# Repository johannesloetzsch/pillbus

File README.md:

## [PillBus](./hw/stm32)

## License

This source describes Open Hardware and is licensed under the [CERN-OHL-S v2](https://ohwr.org/cern_ohl_s_v2.txt)

Should you produce hardware based on this source, you must where practicable maintain the source location visible on the external case of the products.

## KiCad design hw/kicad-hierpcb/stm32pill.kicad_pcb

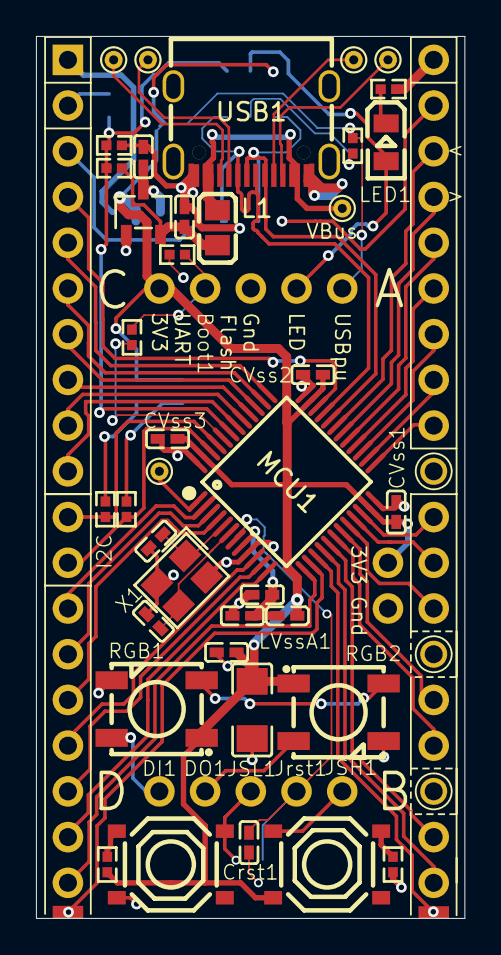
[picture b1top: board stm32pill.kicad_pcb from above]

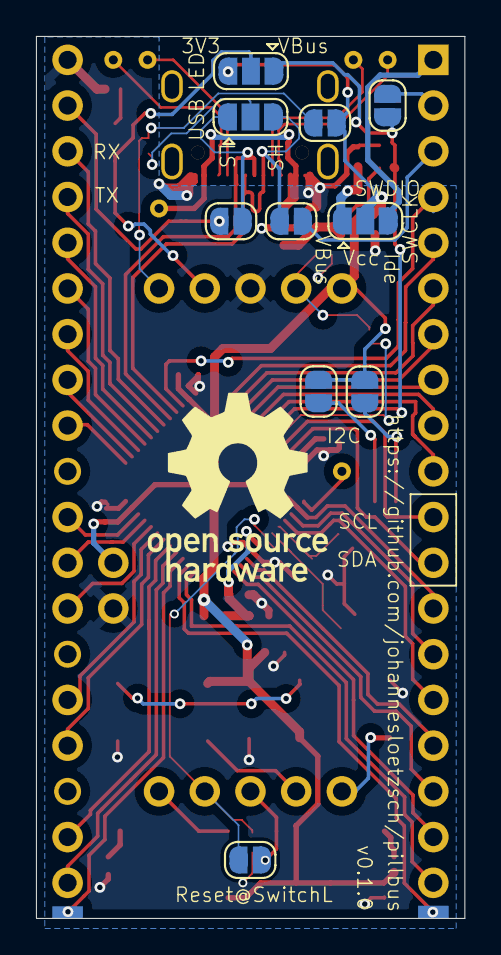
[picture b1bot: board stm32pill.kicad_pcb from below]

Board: 2 copper layers, 23.8 x 49.0 mm, 63 parts (10 on the bottom side), 68 nets.

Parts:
3.3V1: PTH 1.7mm
Boot1: 3x PTH 1.7mm
CC1_1, CC2_1: TestPoint_THTPad_D1.0mm_Drill0.5mm
CLed1: 100nF; C0402
CUin1: 1μF; C0402
CUout1: 1μF; C0402
CVcc1: 4.7uF; C1206
CVss1, CVss2, CVss3: 100nF; C0402
CVssA1: 1μF; C0402
CVssAn1: 10nF; C0402
Cosc1, Cosc2: 30pF; C0402
Crst1: 100nF; C0402
DI1: PTH 1.7mm
DO1: PTH 1.7mm
GND1: PTH 1.7mm
IDE_STM_A1: IDE STM A
IDE_STM_B1: IDE STM B cut
IDE_STM_C1: IDE STM C
IDE_STM_D1: IDE STM D cut
JPLed1: SolderJumper_3_Open; SolderJumper-3_P1.3mm_Open_RoundedPad1.0x1.5mm
JPReset1: SolderJumper_2_Open; SolderJumper-2_P1.3mm_Open_RoundedPad1.0x1.5mm
JPRscl1: SolderJumper_2_Open; SolderJumper-2_P1.3mm_Open_RoundedPad1.0x1.5mm
JPRsda1: SolderJumper_2_Open; SolderJumper-2_P1.3mm_Open_RoundedPad1.0x1.5mm
JPV1: SolderJumper_3_Open; SolderJumper-3_P1.3mm_Open_RoundedPad1.0x1.5mm
JPdn1: SolderJumper_2_Open; SolderJumper-2_P1.3mm_Open_RoundedPad1.0x1.5mm
JPdp1: SolderJumper_2_Open; SolderJumper-2_P1.3mm_Open_RoundedPad1.0x1.5mm
JPpuUSB1: SolderJumper_3_Open; SolderJumper-3_P1.3mm_Open_RoundedPad1.0x1.5mm
JPpuUSBconst1: SolderJumper_2_Open; SolderJumper-2_P1.3mm_Open_RoundedPad1.0x1.5mm
JPvbus1: SolderJumper_2_Open; SolderJumper-2_P1.3mm_Open_RoundedPad1.0x1.5mm
JSH1: PTH 1.7mm
JSL1: PTH 1.7mm
JVbat1: VBAT; TestPoint_THTPad_D1.0mm_Drill0.5mm
Jled1: PTH 1.7mm
JpuUSB1: PTH 1.7mm
Jrst1: PTH 1.7mm
L1: 100Ω@100MHz; L0805
LED1: Green; LED0805-R-RD
LVssA1: 15-30nH; L0402
MCU1: STM32F103C8T6; LQFP-48_L7.0-W7.0-P0.50-LS9.0-BL
RGB1, RGB2: LED WS2812B; LED-SMD_4P-L5.0-W5.0-TL-1
RSBoot1: 51kΩ; R0402
RVbusI1: 51kΩ; R0402
RVbusO1: 100kΩ; R0402
Rled1: 1k-1.5k; R0402
Rpd1: 10kΩ; R0402
Rpu1: 10kΩ; R0402
RpuBoot1: 51kΩ; R0402
RpuUSB1: 1.5kΩ; R0402
Rscl1: 2.2kΩ; R0402
Rsda1: 2.2kΩ; R0402
SBU1_1, SBU2_1: TestPoint_THTPad_D1.0mm_Drill0.5mm
SW1, SW2: Tactile Switch; SW-SMD_4P-L5.1-W5.1-P3.70-LS6.5-TL_H1.5
U1: 3.3V Voltage Regulator 200mA; SOT-23-3_L2.9-W1.6-P1.90-LS2.8-BR
USB1: USB_C; USB-C_SMD-TYPE-C-31-M-12
VBus_1: TestPoint_THTPad_D1.0mm_Drill0.5mm
X1: Crystal 12MHz X322512MSB4SI; CRYSTAL-SMD_4P-L3.2-W2.5-BL

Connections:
+3.3V: 3.3V1.1, Boot1.3, CLed1.2, CVcc1.1, CVss1.2, CVss2.2, CVss3.2, JPLed1.3 (B), JPRscl1.2 (B), JPRsda1.1 (A), JPV1.2 (C), JPpuUSBconst1.2 (B), LVssA1.2, MCU1.23 (VSS_1), MCU1.35 (VSS_2), MCU1.47 (VSS_3), RGB1.1 (VDD), RGB2.1 (VDD), Rpu1.2, SW2.2 (B)
/Boot0: Boot1.2, RSBoot1.2, RpuBoot1.1
/CC1: CC1_1.1, USB1.A5 (CC1)
/CC2: CC2_1.1, USB1.B5 (CC2)
/I2C1 SCL: IDE_STM_D1.SCL (IDE39_STM45), MCU1.45 (PB8), Rscl1.1
/I2C1 SDA: IDE_STM_D1.SDA (IDE37_STM46), MCU1.46 (PB9), Rsda1.1
/I2C2 SCL, USART3 TX: IDE_STM_B1.B1 (IDE24_STM13), MCU1.21 (PB10)
/I2C2 SDA, USART3 RX: IDE_STM_B1.B0 (IDE22_STM14), MCU1.22 (PB11)
/NRST: Crst1.2, JPReset1.1 (A), Jrst1.1, MCU1.7 (NRST)
/OSC_IN: Cosc1.2, MCU1.5 (PD0-OSC_IN), X1.1 (OSC1)
/OSC_OUT: Cosc2.2, MCU1.6 (PD1-OSC_OUT), X1.3 (OSC2)
/SBU1: SBU1_1.1, USB1.A8 (SBU1)
/SBU2: SBU2_1.1, USB1.B8 (SBU2)
/SPI1 MISO: IDE_STM_B1.B6 (IDE38_STM3), MCU1.16 (PA6)
/SPI1 MOSI: IDE_STM_B1.B5 (IDE36_STM4), MCU1.17 (PA7)
/SPI1 SCK: IDE_STM_B1.B7 (IDE40_STM2), MCU1.15 (PA5)
/SPI2 MISO: IDE_STM_A1.A5 (IDE14_STM17), MCU1.27 (PB14)
/SPI2 MOSI: IDE_STM_A1.A4 (IDE12_STM18), MCU1.28 (PB15)
/SPI2 NSS: IDE_STM_A1.A7 (IDE18_STM15), MCU1.25 (PB12)
/SPI2 SCK: IDE_STM_A1.A6 (IDE16_STM16), MCU1.26 (PB13)
/USART1 RX: IDE_STM_A1.A1 (IDE6_STM21), MCU1.31 (PA10)
/USART1 TX: IDE_STM_A1.A2 (IDE8_STM20), MCU1.30 (PA9)
/USB VBusSense: JPLed1.1 (A), JPvbus1.1 (A), MCU1.43 (PB7), RVbusI1.2, RVbusO1.1
/USBd+: JPdp1.2 (B), JPpuUSB1.3 (B), MCU1.33 (PA12), USB1.A6 (DP1), USB1.B6 (DP2)
/USBd-: JPdn1.1 (A), JPpuUSB1.1 (A), MCU1.32 (PA11), USB1.A7 (DN1), USB1.B7 (DN2)
/VBAT: JVbat1.1, MCU1.1 (VBAT)
/VBUS: CUin1.1, L1.1, RVbusI1.1, U1.2 (Vin)
/VSSA: CVssA1.2, CVssAn1.2, LVssA1.1, MCU1.8 (VSSA)
GND: Boot1.1, CLed1.1, CUin1.2, CUout1.2, CVcc1.2, CVss1.1, CVss2.1, CVss3.1, CVssA1.1, CVssAn1.1, Cosc1.1, Cosc2.1, Crst1.1, GND1.1, IDE_STM_A1.GND (IDE2_STM24), MCU1.9 (VDDA), MCU1.24 (VDD_1), MCU1.36 (VDD_2), MCU1.48 (VDD_3), RGB1.3 (GND), RGB2.3 (GND), RVbusO1.2, Rled1.1, Rpd1.1, RpuBoot1.2, SW1.3 (C), U1.1 (GND), USB1.A1 (GND), USB1.A12 (GND), USB1.B1 (GND), USB1.B12 (GND), X1.2 (GND), X1.4 (GND)
unnamed: DI1.1, RGB1.4 (DI)
unnamed: DO1.1, RGB2.2 (DO)
unnamed: IDE_STM_A1.A0 (IDE4_STM22), JPdn1.2 (B)
unnamed: IDE_STM_A1.A3 (IDE10_STM19), MCU1.29 (PA8)
unnamed: IDE_STM_B1.B2 (IDE26_STM12), MCU1.20 (PB2)
unnamed: IDE_STM_B1.B3 (IDE30_STM11), MCU1.19 (PB1)
unnamed: IDE_STM_B1.B4 (IDE32_STM10), MCU1.18 (PB0)
unnamed: IDE_STM_C1.3V3 (IDE1_STM23), JPV1.3 (B)
unnamed: IDE_STM_C1.VBusSense (IDE3_STM43), JPvbus1.2 (B)
unnamed: IDE_STM_C1.C0 (IDE5_STM25), JPdp1.1 (A)
unnamed: IDE_STM_C1.C1 (IDE7_STM26), MCU1.34 (PA13)
unnamed: IDE_STM_C1.C2 (IDE9_STM27), MCU1.37 (PA14)
unnamed: IDE_STM_C1.C3 (IDE11_STM28), MCU1.38 (PA15)
unnamed: IDE_STM_C1.C4 (IDE13_STM29), MCU1.39 (PB3)
unnamed: IDE_STM_C1.C5 (IDE15_STM30), MCU1.40 (PB4)
unnamed: IDE_STM_C1.C6 (IDE17_STM31), MCU1.41 (PB5)
unnamed: IDE_STM_C1.C7 (IDE19_STM32), MCU1.42 (PB6)
unnamed: IDE_STM_D1.D7 (IDE21_STM33), MCU1.14 (PA4)
unnamed: IDE_STM_D1.D6 (IDE23_STM34), MCU1.13 (PA3)
unnamed: IDE_STM_D1.D5 (IDE25_STM37), MCU1.12 (PA2)
unnamed: IDE_STM_D1.D4 (IDE27_STM38), MCU1.11 (PA1)
unnamed: IDE_STM_D1.D3 (IDE29_STM39), MCU1.10 (PA0-WKUP)
unnamed: IDE_STM_D1.D2 (IDE31_STM40), MCU1.4 (PC15-OSC32_OUT)
unnamed: IDE_STM_D1.D1 (IDE33_STM41), MCU1.3 (PC14-OSC32_IN)
unnamed: IDE_STM_D1.D0 (IDE35_STM42), MCU1.2 (PC13-TAMPER-RTC)
unnamed: JPLed1.2 (C), Jled1.1, LED1.1 (A)
unnamed: JPReset1.2 (B), JSL1.1, SW1.2 (B)
unnamed: JPRscl1.1 (A), Rscl1.2
unnamed: JPRsda1.2 (B), Rsda1.2
unnamed: CUout1.1, JPV1.1 (A), U1.3 (Vout)
unnamed: JPpuUSB1.2 (C), RpuUSB1.1
unnamed: JPpuUSBconst1.1 (A), JpuUSB1.1, RpuUSB1.2
unnamed: JSH1.1, SW2.4 (D)
unnamed: LED1.2 (K), Rled1.2
unnamed: MCU1.44 (BOOT0), RSBoot1.1
unnamed: RGB1.2 (DO), RGB2.4 (DI)
unnamed: Rpu1.1, SW1.1 (A)
unnamed: Rpd1.2, SW2.3 (C)
unnamed: L1.2, USB1.A4 (VBUS), USB1.A9 (VBUS), USB1.B4 (VBUS), USB1.B9 (VBUS), VBus_1.1

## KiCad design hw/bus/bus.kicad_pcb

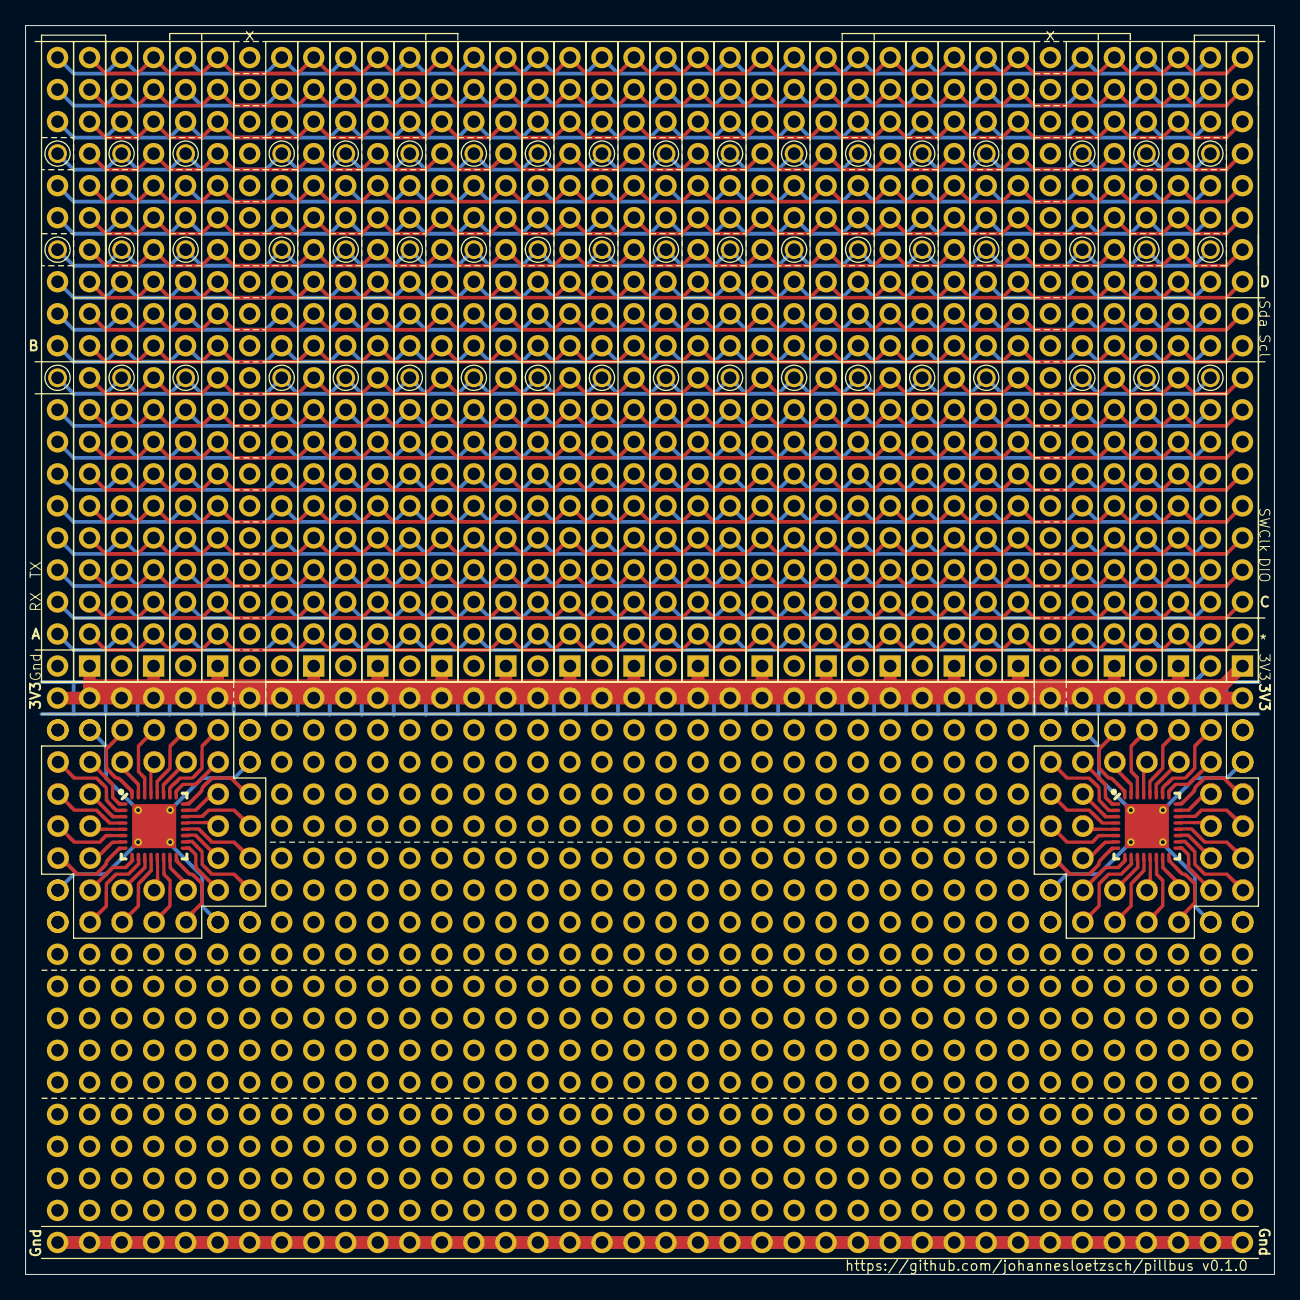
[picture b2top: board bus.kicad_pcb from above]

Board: 2 copper layers, 99.1 x 99.1 mm, 58 parts (0 on the bottom side), 40 nets.

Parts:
Gnd1, Gnd2, Gnd3, Gnd4, Gnd5, Gnd6, Gnd7, Gnd8, Gnd9, Gnd10, Gnd11, Gnd12, Gnd13, Gnd14, Gnd15, Gnd16, Gnd17, Gnd18, Gnd19, Gnd20, Gnd21, Gnd22, Gnd23, Gnd24, Gnd25, Gnd26, Gnd27, Gnd28, Gnd29, Gnd30, Gnd31, Gnd32, Gnd33, Gnd34, Gnd35, Gnd36, Gnd37, Gnd38: PTH 1.7mm
J1, J2, J3, J4, J5, J6, J7, J11, J11#2, J11#3, J11#4, J11#5, J12, J13, J14, J15, J16, J17: IDE STM bus
U***: QFN-32; Breakout QFN-32
U***#2: QFN-32; Breakout QFN-32

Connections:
+3.3V: J1.3V3 (IDE1_STM23), J2.3V3 (IDE1_STM23), J3.3V3 (IDE1_STM23), J4.3V3 (IDE1_STM23), J5.3V3 (IDE1_STM23), J6.3V3 (IDE1_STM23), J7.3V3 (IDE1_STM23), J11.3V3 (IDE1_STM23), J11#2.3V3 (IDE1_STM23), J11#3.3V3 (IDE1_STM23), J11#4.3V3 (IDE1_STM23), J11#5.3V3 (IDE1_STM23), J12.3V3 (IDE1_STM23), J13.3V3 (IDE1_STM23), J14.3V3 (IDE1_STM23), J15.3V3 (IDE1_STM23), J16.3V3 (IDE1_STM23), J17.3V3 (IDE1_STM23)
/A0: J1.A0 (IDE4_STM22), J2.A0 (IDE4_STM22), J3.A0 (IDE4_STM22), J4.A0 (IDE4_STM22), J5.A0 (IDE4_STM22), J6.A0 (IDE4_STM22), J7.A0 (IDE4_STM22), J11.A0 (IDE4_STM22), J11#2.A0 (IDE4_STM22), J11#3.A0 (IDE4_STM22), J11#4.A0 (IDE4_STM22), J11#5.A0 (IDE4_STM22), J12.A0 (IDE4_STM22), J13.A0 (IDE4_STM22), J14.A0 (IDE4_STM22), J15.A0 (IDE4_STM22), J16.A0 (IDE4_STM22), J17.A0 (IDE4_STM22)
/A1: J1.A1 (IDE6_STM21), J2.A1 (IDE6_STM21), J3.A1 (IDE6_STM21), J4.A1 (IDE6_STM21), J5.A1 (IDE6_STM21), J6.A1 (IDE6_STM21), J7.A1 (IDE6_STM21), J11.A1 (IDE6_STM21), J11#2.A1 (IDE6_STM21), J11#3.A1 (IDE6_STM21), J11#4.A1 (IDE6_STM21), J11#5.A1 (IDE6_STM21), J12.A1 (IDE6_STM21), J13.A1 (IDE6_STM21), J14.A1 (IDE6_STM21), J15.A1 (IDE6_STM21), J16.A1 (IDE6_STM21), J17.A1 (IDE6_STM21)
/A2: J1.A2 (IDE8_STM20), J2.A2 (IDE8_STM20), J3.A2 (IDE8_STM20), J4.A2 (IDE8_STM20), J5.A2 (IDE8_STM20), J6.A2 (IDE8_STM20), J7.A2 (IDE8_STM20), J11.A2 (IDE8_STM20), J11#2.A2 (IDE8_STM20), J11#3.A2 (IDE8_STM20), J11#4.A2 (IDE8_STM20), J11#5.A2 (IDE8_STM20), J12.A2 (IDE8_STM20), J13.A2 (IDE8_STM20), J14.A2 (IDE8_STM20), J15.A2 (IDE8_STM20), J16.A2 (IDE8_STM20), J17.A2 (IDE8_STM20)
/A3: J1.A3 (IDE10_STM19), J2.A3 (IDE10_STM19), J3.A3 (IDE10_STM19), J4.A3 (IDE10_STM19), J5.A3 (IDE10_STM19), J6.A3 (IDE10_STM19), J7.A3 (IDE10_STM19), J11.A3 (IDE10_STM19), J11#2.A3 (IDE10_STM19), J11#3.A3 (IDE10_STM19), J11#4.A3 (IDE10_STM19), J11#5.A3 (IDE10_STM19), J12.A3 (IDE10_STM19), J13.A3 (IDE10_STM19), J14.A3 (IDE10_STM19), J15.A3 (IDE10_STM19), J16.A3 (IDE10_STM19), J17.A3 (IDE10_STM19)
/A4: J1.A4 (IDE12_STM18), J2.A4 (IDE12_STM18), J3.A4 (IDE12_STM18), J4.A4 (IDE12_STM18), J5.A4 (IDE12_STM18), J6.A4 (IDE12_STM18), J7.A4 (IDE12_STM18), J11.A4 (IDE12_STM18), J11#2.A4 (IDE12_STM18), J11#3.A4 (IDE12_STM18), J11#4.A4 (IDE12_STM18), J11#5.A4 (IDE12_STM18), J12.A4 (IDE12_STM18), J13.A4 (IDE12_STM18), J14.A4 (IDE12_STM18), J15.A4 (IDE12_STM18), J16.A4 (IDE12_STM18), J17.A4 (IDE12_STM18)
/A5: J1.A5 (IDE14_STM17), J2.A5 (IDE14_STM17), J3.A5 (IDE14_STM17), J4.A5 (IDE14_STM17), J5.A5 (IDE14_STM17), J6.A5 (IDE14_STM17), J7.A5 (IDE14_STM17), J11.A5 (IDE14_STM17), J11#2.A5 (IDE14_STM17), J11#3.A5 (IDE14_STM17), J11#4.A5 (IDE14_STM17), J11#5.A5 (IDE14_STM17), J12.A5 (IDE14_STM17), J13.A5 (IDE14_STM17), J14.A5 (IDE14_STM17), J15.A5 (IDE14_STM17), J16.A5 (IDE14_STM17), J17.A5 (IDE14_STM17)
/A6: J1.A6 (IDE16_STM16), J2.A6 (IDE16_STM16), J3.A6 (IDE16_STM16), J4.A6 (IDE16_STM16), J5.A6 (IDE16_STM16), J6.A6 (IDE16_STM16), J7.A6 (IDE16_STM16), J11.A6 (IDE16_STM16), J11#2.A6 (IDE16_STM16), J11#3.A6 (IDE16_STM16), J11#4.A6 (IDE16_STM16), J11#5.A6 (IDE16_STM16), J12.A6 (IDE16_STM16), J13.A6 (IDE16_STM16), J14.A6 (IDE16_STM16), J15.A6 (IDE16_STM16), J16.A6 (IDE16_STM16), J17.A6 (IDE16_STM16)
/A7: J1.A7 (IDE18_STM15), J2.A7 (IDE18_STM15), J3.A7 (IDE18_STM15), J4.A7 (IDE18_STM15), J5.A7 (IDE18_STM15), J6.A7 (IDE18_STM15), J7.A7 (IDE18_STM15), J11.A7 (IDE18_STM15), J11#2.A7 (IDE18_STM15), J11#3.A7 (IDE18_STM15), J11#4.A7 (IDE18_STM15), J11#5.A7 (IDE18_STM15), J12.A7 (IDE18_STM15), J13.A7 (IDE18_STM15), J14.A7 (IDE18_STM15), J15.A7 (IDE18_STM15), J16.A7 (IDE18_STM15), J17.A7 (IDE18_STM15)
/B0: J1.B0 (IDE22_STM14), J2.B0 (IDE22_STM14), J3.B0 (IDE22_STM14), J4.B0 (IDE22_STM14), J5.B0 (IDE22_STM14), J6.B0 (IDE22_STM14), J7.B0 (IDE22_STM14), J11.B0 (IDE22_STM14), J11#2.B0 (IDE22_STM14), J11#3.B0 (IDE22_STM14), J11#4.B0 (IDE22_STM14), J11#5.B0 (IDE22_STM14), J12.B0 (IDE22_STM14), J13.B0 (IDE22_STM14), J14.B0 (IDE22_STM14), J15.B0 (IDE22_STM14), J16.B0 (IDE22_STM14), J17.B0 (IDE22_STM14)
/B1: J1.B1 (IDE24_STM13), J2.B1 (IDE24_STM13), J3.B1 (IDE24_STM13), J4.B1 (IDE24_STM13), J5.B1 (IDE24_STM13), J6.B1 (IDE24_STM13), J7.B1 (IDE24_STM13), J11.B1 (IDE24_STM13), J11#2.B1 (IDE24_STM13), J11#3.B1 (IDE24_STM13), J11#4.B1 (IDE24_STM13), J11#5.B1 (IDE24_STM13), J12.B1 (IDE24_STM13), J13.B1 (IDE24_STM13), J14.B1 (IDE24_STM13), J15.B1 (IDE24_STM13), J16.B1 (IDE24_STM13), J17.B1 (IDE24_STM13)
/B2: J1.B2 (IDE26_STM12), J2.B2 (IDE26_STM12), J3.B2 (IDE26_STM12), J4.B2 (IDE26_STM12), J5.B2 (IDE26_STM12), J6.B2 (IDE26_STM12), J7.B2 (IDE26_STM12), J11.B2 (IDE26_STM12), J11#2.B2 (IDE26_STM12), J11#3.B2 (IDE26_STM12), J11#4.B2 (IDE26_STM12), J11#5.B2 (IDE26_STM12), J12.B2 (IDE26_STM12), J13.B2 (IDE26_STM12), J14.B2 (IDE26_STM12), J15.B2 (IDE26_STM12), J16.B2 (IDE26_STM12), J17.B2 (IDE26_STM12)
/B3: J1.B3 (IDE30_STM11), J2.B3 (IDE30_STM11), J3.B3 (IDE30_STM11), J4.B3 (IDE30_STM11), J5.B3 (IDE30_STM11), J6.B3 (IDE30_STM11), J7.B3 (IDE30_STM11), J11.B3 (IDE30_STM11), J11#2.B3 (IDE30_STM11), J11#3.B3 (IDE30_STM11), J11#4.B3 (IDE30_STM11), J11#5.B3 (IDE30_STM11), J12.B3 (IDE30_STM11), J13.B3 (IDE30_STM11), J14.B3 (IDE30_STM11), J15.B3 (IDE30_STM11), J16.B3 (IDE30_STM11), J17.B3 (IDE30_STM11)
/B4: J1.B4 (IDE32_STM10), J2.B4 (IDE32_STM10), J3.B4 (IDE32_STM10), J4.B4 (IDE32_STM10), J5.B4 (IDE32_STM10), J6.B4 (IDE32_STM10), J7.B4 (IDE32_STM10), J11.B4 (IDE32_STM10), J11#2.B4 (IDE32_STM10), J11#3.B4 (IDE32_STM10), J11#4.B4 (IDE32_STM10), J11#5.B4 (IDE32_STM10), J12.B4 (IDE32_STM10), J13.B4 (IDE32_STM10), J14.B4 (IDE32_STM10), J15.B4 (IDE32_STM10), J16.B4 (IDE32_STM10), J17.B4 (IDE32_STM10)
/B5: J1.B5 (IDE36_STM4), J2.B5 (IDE36_STM4), J3.B5 (IDE36_STM4), J4.B5 (IDE36_STM4), J5.B5 (IDE36_STM4), J6.B5 (IDE36_STM4), J7.B5 (IDE36_STM4), J11.B5 (IDE36_STM4), J11#2.B5 (IDE36_STM4), J11#3.B5 (IDE36_STM4), J11#4.B5 (IDE36_STM4), J11#5.B5 (IDE36_STM4), J12.B5 (IDE36_STM4), J13.B5 (IDE36_STM4), J14.B5 (IDE36_STM4), J15.B5 (IDE36_STM4), J16.B5 (IDE36_STM4), J17.B5 (IDE36_STM4)
/B6: J1.B6 (IDE38_STM3), J2.B6 (IDE38_STM3), J3.B6 (IDE38_STM3), J4.B6 (IDE38_STM3), J5.B6 (IDE38_STM3), J6.B6 (IDE38_STM3), J7.B6 (IDE38_STM3), J11.B6 (IDE38_STM3), J11#2.B6 (IDE38_STM3), J11#3.B6 (IDE38_STM3), J11#4.B6 (IDE38_STM3), J11#5.B6 (IDE38_STM3), J12.B6 (IDE38_STM3), J13.B6 (IDE38_STM3), J14.B6 (IDE38_STM3), J15.B6 (IDE38_STM3), J16.B6 (IDE38_STM3), J17.B6 (IDE38_STM3)
/B7: J1.B7 (IDE40_STM2), J2.B7 (IDE40_STM2), J3.B7 (IDE40_STM2), J4.B7 (IDE40_STM2), J5.B7 (IDE40_STM2), J6.B7 (IDE40_STM2), J7.B7 (IDE40_STM2), J11.B7 (IDE40_STM2), J11#2.B7 (IDE40_STM2), J11#3.B7 (IDE40_STM2), J11#4.B7 (IDE40_STM2), J11#5.B7 (IDE40_STM2), J12.B7 (IDE40_STM2), J13.B7 (IDE40_STM2), J14.B7 (IDE40_STM2), J15.B7 (IDE40_STM2), J16.B7 (IDE40_STM2), J17.B7 (IDE40_STM2)
/C0: J1.C0 (IDE5_STM25), J2.C0 (IDE5_STM25), J3.C0 (IDE5_STM25), J4.C0 (IDE5_STM25), J5.C0 (IDE5_STM25), J6.C0 (IDE5_STM25), J7.C0 (IDE5_STM25), J11.C0 (IDE5_STM25), J11#2.C0 (IDE5_STM25), J11#3.C0 (IDE5_STM25), J11#4.C0 (IDE5_STM25), J11#5.C0 (IDE5_STM25), J12.C0 (IDE5_STM25), J13.C0 (IDE5_STM25), J14.C0 (IDE5_STM25), J15.C0 (IDE5_STM25), J16.C0 (IDE5_STM25), J17.C0 (IDE5_STM25)
/C1: J1.C1 (IDE7_STM26), J2.C1 (IDE7_STM26), J3.C1 (IDE7_STM26), J4.C1 (IDE7_STM26), J5.C1 (IDE7_STM26), J6.C1 (IDE7_STM26), J7.C1 (IDE7_STM26), J11.C1 (IDE7_STM26), J11#2.C1 (IDE7_STM26), J11#3.C1 (IDE7_STM26), J11#4.C1 (IDE7_STM26), J11#5.C1 (IDE7_STM26), J12.C1 (IDE7_STM26), J13.C1 (IDE7_STM26), J14.C1 (IDE7_STM26), J15.C1 (IDE7_STM26), J16.C1 (IDE7_STM26), J17.C1 (IDE7_STM26)
/C2: J1.C2 (IDE9_STM27), J2.C2 (IDE9_STM27), J3.C2 (IDE9_STM27), J4.C2 (IDE9_STM27), J5.C2 (IDE9_STM27), J6.C2 (IDE9_STM27), J7.C2 (IDE9_STM27), J11.C2 (IDE9_STM27), J11#2.C2 (IDE9_STM27), J11#3.C2 (IDE9_STM27), J11#4.C2 (IDE9_STM27), J11#5.C2 (IDE9_STM27), J12.C2 (IDE9_STM27), J13.C2 (IDE9_STM27), J14.C2 (IDE9_STM27), J15.C2 (IDE9_STM27), J16.C2 (IDE9_STM27), J17.C2 (IDE9_STM27)
/C3: J1.C3 (IDE11_STM28), J2.C3 (IDE11_STM28), J3.C3 (IDE11_STM28), J4.C3 (IDE11_STM28), J5.C3 (IDE11_STM28), J6.C3 (IDE11_STM28), J7.C3 (IDE11_STM28), J11.C3 (IDE11_STM28), J11#2.C3 (IDE11_STM28), J11#3.C3 (IDE11_STM28), J11#4.C3 (IDE11_STM28), J11#5.C3 (IDE11_STM28), J12.C3 (IDE11_STM28), J13.C3 (IDE11_STM28), J14.C3 (IDE11_STM28), J15.C3 (IDE11_STM28), J16.C3 (IDE11_STM28), J17.C3 (IDE11_STM28)
/C4: J1.C4 (IDE13_STM29), J2.C4 (IDE13_STM29), J3.C4 (IDE13_STM29), J4.C4 (IDE13_STM29), J5.C4 (IDE13_STM29), J6.C4 (IDE13_STM29), J7.C4 (IDE13_STM29), J11.C4 (IDE13_STM29), J11#2.C4 (IDE13_STM29), J11#3.C4 (IDE13_STM29), J11#4.C4 (IDE13_STM29), J11#5.C4 (IDE13_STM29), J12.C4 (IDE13_STM29), J13.C4 (IDE13_STM29), J14.C4 (IDE13_STM29), J15.C4 (IDE13_STM29), J16.C4 (IDE13_STM29), J17.C4 (IDE13_STM29)
/C5: J1.C5 (IDE15_STM30), J2.C5 (IDE15_STM30), J3.C5 (IDE15_STM30), J4.C5 (IDE15_STM30), J5.C5 (IDE15_STM30), J6.C5 (IDE15_STM30), J7.C5 (IDE15_STM30), J11.C5 (IDE15_STM30), J11#2.C5 (IDE15_STM30), J11#3.C5 (IDE15_STM30), J11#4.C5 (IDE15_STM30), J11#5.C5 (IDE15_STM30), J12.C5 (IDE15_STM30), J13.C5 (IDE15_STM30), J14.C5 (IDE15_STM30), J15.C5 (IDE15_STM30), J16.C5 (IDE15_STM30), J17.C5 (IDE15_STM30)
/C6: J1.C6 (IDE17_STM31), J2.C6 (IDE17_STM31), J3.C6 (IDE17_STM31), J4.C6 (IDE17_STM31), J5.C6 (IDE17_STM31), J6.C6 (IDE17_STM31), J7.C6 (IDE17_STM31), J11.C6 (IDE17_STM31), J11#2.C6 (IDE17_STM31), J11#3.C6 (IDE17_STM31), J11#4.C6 (IDE17_STM31), J11#5.C6 (IDE17_STM31), J12.C6 (IDE17_STM31), J13.C6 (IDE17_STM31), J14.C6 (IDE17_STM31), J15.C6 (IDE17_STM31), J16.C6 (IDE17_STM31), J17.C6 (IDE17_STM31)
/C7: J1.C7 (IDE19_STM32), J2.C7 (IDE19_STM32), J3.C7 (IDE19_STM32), J4.C7 (IDE19_STM32), J5.C7 (IDE19_STM32), J6.C7 (IDE19_STM32), J7.C7 (IDE19_STM32), J11.C7 (IDE19_STM32), J11#2.C7 (IDE19_STM32), J11#3.C7 (IDE19_STM32), J11#4.C7 (IDE19_STM32), J11#5.C7 (IDE19_STM32), J12.C7 (IDE19_STM32), J13.C7 (IDE19_STM32), J14.C7 (IDE19_STM32), J15.C7 (IDE19_STM32), J16.C7 (IDE19_STM32), J17.C7 (IDE19_STM32)
/D0: J1.D0 (IDE35_STM42), J2.D0 (IDE35_STM42), J3.D0 (IDE35_STM42), J4.D0 (IDE35_STM42), J5.D0 (IDE35_STM42), J6.D0 (IDE35_STM42), J7.D0 (IDE35_STM42), J11.D0 (IDE35_STM42), J11#2.D0 (IDE35_STM42), J11#3.D0 (IDE35_STM42), J11#4.D0 (IDE35_STM42), J11#5.D0 (IDE35_STM42), J12.D0 (IDE35_STM42), J13.D0 (IDE35_STM42), J14.D0 (IDE35_STM42), J15.D0 (IDE35_STM42), J16.D0 (IDE35_STM42), J17.D0 (IDE35_STM42)
/D1: J1.D1 (IDE33_STM41), J2.D1 (IDE33_STM41), J3.D1 (IDE33_STM41), J4.D1 (IDE33_STM41), J5.D1 (IDE33_STM41), J6.D1 (IDE33_STM41), J7.D1 (IDE33_STM41), J11.D1 (IDE33_STM41), J11#2.D1 (IDE33_STM41), J11#3.D1 (IDE33_STM41), J11#4.D1 (IDE33_STM41), J11#5.D1 (IDE33_STM41), J12.D1 (IDE33_STM41), J13.D1 (IDE33_STM41), J14.D1 (IDE33_STM41), J15.D1 (IDE33_STM41), J16.D1 (IDE33_STM41), J17.D1 (IDE33_STM41)
/D2: J1.D2 (IDE31_STM40), J2.D2 (IDE31_STM40), J3.D2 (IDE31_STM40), J4.D2 (IDE31_STM40), J5.D2 (IDE31_STM40), J6.D2 (IDE31_STM40), J7.D2 (IDE31_STM40), J11.D2 (IDE31_STM40), J11#2.D2 (IDE31_STM40), J11#3.D2 (IDE31_STM40), J11#4.D2 (IDE31_STM40), J11#5.D2 (IDE31_STM40), J12.D2 (IDE31_STM40), J13.D2 (IDE31_STM40), J14.D2 (IDE31_STM40), J15.D2 (IDE31_STM40), J16.D2 (IDE31_STM40), J17.D2 (IDE31_STM40)
/D3: J1.D3 (IDE29_STM39), J2.D3 (IDE29_STM39), J3.D3 (IDE29_STM39), J4.D3 (IDE29_STM39), J5.D3 (IDE29_STM39), J6.D3 (IDE29_STM39), J7.D3 (IDE29_STM39), J11.D3 (IDE29_STM39), J11#2.D3 (IDE29_STM39), J11#3.D3 (IDE29_STM39), J11#4.D3 (IDE29_STM39), J11#5.D3 (IDE29_STM39), J12.D3 (IDE29_STM39), J13.D3 (IDE29_STM39), J14.D3 (IDE29_STM39), J15.D3 (IDE29_STM39), J16.D3 (IDE29_STM39), J17.D3 (IDE29_STM39)
/D4: J1.D4 (IDE27_STM38), J2.D4 (IDE27_STM38), J3.D4 (IDE27_STM38), J4.D4 (IDE27_STM38), J5.D4 (IDE27_STM38), J6.D4 (IDE27_STM38), J7.D4 (IDE27_STM38), J11.D4 (IDE27_STM38), J11#2.D4 (IDE27_STM38), J11#3.D4 (IDE27_STM38), J11#4.D4 (IDE27_STM38), J11#5.D4 (IDE27_STM38), J12.D4 (IDE27_STM38), J13.D4 (IDE27_STM38), J14.D4 (IDE27_STM38), J15.D4 (IDE27_STM38), J16.D4 (IDE27_STM38), J17.D4 (IDE27_STM38)
/D5: J1.D5 (IDE25_STM37), J2.D5 (IDE25_STM37), J3.D5 (IDE25_STM37), J4.D5 (IDE25_STM37), J5.D5 (IDE25_STM37), J6.D5 (IDE25_STM37), J7.D5 (IDE25_STM37), J11.D5 (IDE25_STM37), J11#2.D5 (IDE25_STM37), J11#3.D5 (IDE25_STM37), J11#4.D5 (IDE25_STM37), J11#5.D5 (IDE25_STM37), J12.D5 (IDE25_STM37), J13.D5 (IDE25_STM37), J14.D5 (IDE25_STM37), J15.D5 (IDE25_STM37), J16.D5 (IDE25_STM37), J17.D5 (IDE25_STM37)
/D6: J1.D6 (IDE23_STM34), J2.D6 (IDE23_STM34), J3.D6 (IDE23_STM34), J4.D6 (IDE23_STM34), J5.D6 (IDE23_STM34), J6.D6 (IDE23_STM34), J7.D6 (IDE23_STM34), J11.D6 (IDE23_STM34), J11#2.D6 (IDE23_STM34), J11#3.D6 (IDE23_STM34), J11#4.D6 (IDE23_STM34), J11#5.D6 (IDE23_STM34), J12.D6 (IDE23_STM34), J13.D6 (IDE23_STM34), J14.D6 (IDE23_STM34), J15.D6 (IDE23_STM34), J16.D6 (IDE23_STM34), J17.D6 (IDE23_STM34)
/D7: J1.D7 (IDE21_STM33), J2.D7 (IDE21_STM33), J3.D7 (IDE21_STM33), J4.D7 (IDE21_STM33), J5.D7 (IDE21_STM33), J6.D7 (IDE21_STM33), J7.D7 (IDE21_STM33), J11.D7 (IDE21_STM33), J11#2.D7 (IDE21_STM33), J11#3.D7 (IDE21_STM33), J11#4.D7 (IDE21_STM33), J11#5.D7 (IDE21_STM33), J12.D7 (IDE21_STM33), J13.D7 (IDE21_STM33), J14.D7 (IDE21_STM33), J15.D7 (IDE21_STM33), J16.D7 (IDE21_STM33), J17.D7 (IDE21_STM33)
/SCL: J1.SCL (IDE37_STM46), J2.SCL (IDE37_STM46), J3.SCL (IDE37_STM46), J4.SCL (IDE37_STM46), J5.SCL (IDE37_STM46), J6.SCL (IDE37_STM46), J7.SCL (IDE37_STM46), J11.SCL (IDE37_STM46), J11#2.SCL (IDE37_STM46), J11#3.SCL (IDE37_STM46), J11#4.SCL (IDE37_STM46), J11#5.SCL (IDE37_STM46), J12.SCL (IDE37_STM46), J13.SCL (IDE37_STM46), J14.SCL (IDE37_STM46), J15.SCL (IDE37_STM46), J16.SCL (IDE37_STM46), J17.SCL (IDE37_STM46)
/SDA: J1.SDA (IDE39_STM45), J2.SDA (IDE39_STM45), J3.SDA (IDE39_STM45), J4.SDA (IDE39_STM45), J5.SDA (IDE39_STM45), J6.SDA (IDE39_STM45), J7.SDA (IDE39_STM45), J11.SDA (IDE39_STM45), J11#2.SDA (IDE39_STM45), J11#3.SDA (IDE39_STM45), J11#4.SDA (IDE39_STM45), J11#5.SDA (IDE39_STM45), J12.SDA (IDE39_STM45), J13.SDA (IDE39_STM45), J14.SDA (IDE39_STM45), J15.SDA (IDE39_STM45), J16.SDA (IDE39_STM45), J17.SDA (IDE39_STM45)
/VBusSense: J1.VBusSense (IDE3_STM43), J2.VBusSense (IDE3_STM43), J3.VBusSense (IDE3_STM43), J4.VBusSense (IDE3_STM43), J5.VBusSense (IDE3_STM43), J6.VBusSense (IDE3_STM43), J7.VBusSense (IDE3_STM43), J11.VBusSense (IDE3_STM43), J11#2.VBusSense (IDE3_STM43), J11#3.VBusSense (IDE3_STM43), J11#4.VBusSense (IDE3_STM43), J11#5.VBusSense (IDE3_STM43), J12.VBusSense (IDE3_STM43), J13.VBusSense (IDE3_STM43), J14.VBusSense (IDE3_STM43), J15.VBusSense (IDE3_STM43), J16.VBusSense (IDE3_STM43), J17.VBusSense (IDE3_STM43)
/x20: J1.x20 (20_mechanical_key), J2.x20 (20_mechanical_key), J3.x20 (20_mechanical_key), J4.x20 (20_mechanical_key), J5.x20 (20_mechanical_key), J6.x20 (20_mechanical_key), J7.x20 (20_mechanical_key), J11.x20 (20_mechanical_key), J11#2.x20 (20_mechanical_key), J11#3.x20 (20_mechanical_key), J11#4.x20 (20_mechanical_key), J11#5.x20 (20_mechanical_key), J12.x20 (20_mechanical_key), J13.x20 (20_mechanical_key), J14.x20 (20_mechanical_key), J15.x20 (20_mechanical_key), J16.x20 (20_mechanical_key), J17.x20 (20_mechanical_key)
/x28: J1.x28 (28_cable_select), J2.x28 (28_cable_select), J3.x28 (28_cable_select), J4.x28 (28_cable_select), J5.x28 (28_cable_select), J6.x28 (28_cable_select), J7.x28 (28_cable_select), J11.x28 (28_cable_select), J11#2.x28 (28_cable_select), J11#3.x28 (28_cable_select), J11#4.x28 (28_cable_select), J11#5.x28 (28_cable_select), J12.x28 (28_cable_select), J13.x28 (28_cable_select), J14.x28 (28_cable_select), J15.x28 (28_cable_select), J16.x28 (28_cable_select), J17.x28 (28_cable_select)
/x34: J1.x34 (34_blue_connector), J2.x34 (34_blue_connector), J3.x34 (34_blue_connector), J4.x34 (34_blue_connector), J5.x34 (34_blue_connector), J6.x34 (34_blue_connector), J7.x34 (34_blue_connector), J11.x34 (34_blue_connector), J11#2.x34 (34_blue_connector), J11#3.x34 (34_blue_connector), J11#4.x34 (34_blue_connector), J11#5.x34 (34_blue_connector), J12.x34 (34_blue_connector), J13.x34 (34_blue_connector), J14.x34 (34_blue_connector), J15.x34 (34_blue_connector), J16.x34 (34_blue_connector), J17.x34 (34_blue_connector)
GND: Gnd1.1, Gnd2.1, Gnd3.1, Gnd4.1, Gnd5.1, Gnd6.1, Gnd7.1, Gnd8.1, Gnd9.1, Gnd10.1, Gnd11.1, Gnd12.1, Gnd13.1, Gnd14.1, Gnd15.1, Gnd16.1, Gnd17.1, Gnd18.1, Gnd19.1, Gnd20.1, Gnd21.1, Gnd22.1, Gnd23.1, Gnd24.1, Gnd25.1, Gnd26.1, Gnd27.1, Gnd28.1, Gnd29.1, Gnd30.1, Gnd31.1, Gnd32.1, Gnd33.1, Gnd34.1, Gnd35.1, Gnd36.1, Gnd37.1, Gnd38.1, J1.GND (IDE2_STM24), J2.GND (IDE2_STM24), J3.GND (IDE2_STM24), J4.GND (IDE2_STM24), J5.GND (IDE2_STM24), J6.GND (IDE2_STM24), J7.GND (IDE2_STM24), J11.GND (IDE2_STM24), J11#2.GND (IDE2_STM24), J11#3.GND (IDE2_STM24), J11#4.GND (IDE2_STM24), J11#5.GND (IDE2_STM24), J12.GND (IDE2_STM24), J13.GND (IDE2_STM24), J14.GND (IDE2_STM24), J15.GND (IDE2_STM24), J16.GND (IDE2_STM24), J17.GND (IDE2_STM24)
